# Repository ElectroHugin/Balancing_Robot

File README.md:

# Balancing_Robot

## Description
Self balancing robot with two wheels. Scope of functionality depends on sensors and is still work in progress.

## Materials
- ESP32 Dev Kit C V4 mit CP2102
- Later on custom board with ESP32-S3-WROOM
- SiliconLabs Uart-to-USB CP2102
- ~~Accelerometer / Gyroscope / Magnetometer BNO085~~
- Accelerometer / Gyroscope MPU6050
- VL53L0X Time-of-Flight (TOF) Laser distance sensor
- (HC-SR04 Ultrasound Module)
- (MAX7219 8x8 1 Dot Matrix MCU LED Display Module)
- ~~BMP180 Barometric Air Pressure and Temperature Sensor~~
- ~~DHT22 Temperature Sensor and Humidity Sensor~~
- ~~Photo LDR Resistor Diodes~~
- ~~L298N H-Bridge Motor Driver~~
- TB6612FNG Motor Driver
- USB-C PD with Battery
- ~~MT3608 DC-DC power supply adapter step up module~~
    ~~- Input voltage: 2V - 24V~~
    ~~- Output voltage: 3V - 28V~~
- ~~OR M2596S Step-down DC-DC Buck Converter~~
    ~~-  Input voltage: 4-40V~~
    ~~-  Output voltage: 3.3-24V~~
- JGA25-371 DC-Motor 12V with Hall-Encoder 65mm wheels

## Visuals
### 3D Model

### PCB Models

## Installation
WIP

## Usage
WIP

## License
Licenses under GNU GENERAL PUBLIC LICENSE Version 3, 29 June 2007

## Project status
Still at the beginning of project.

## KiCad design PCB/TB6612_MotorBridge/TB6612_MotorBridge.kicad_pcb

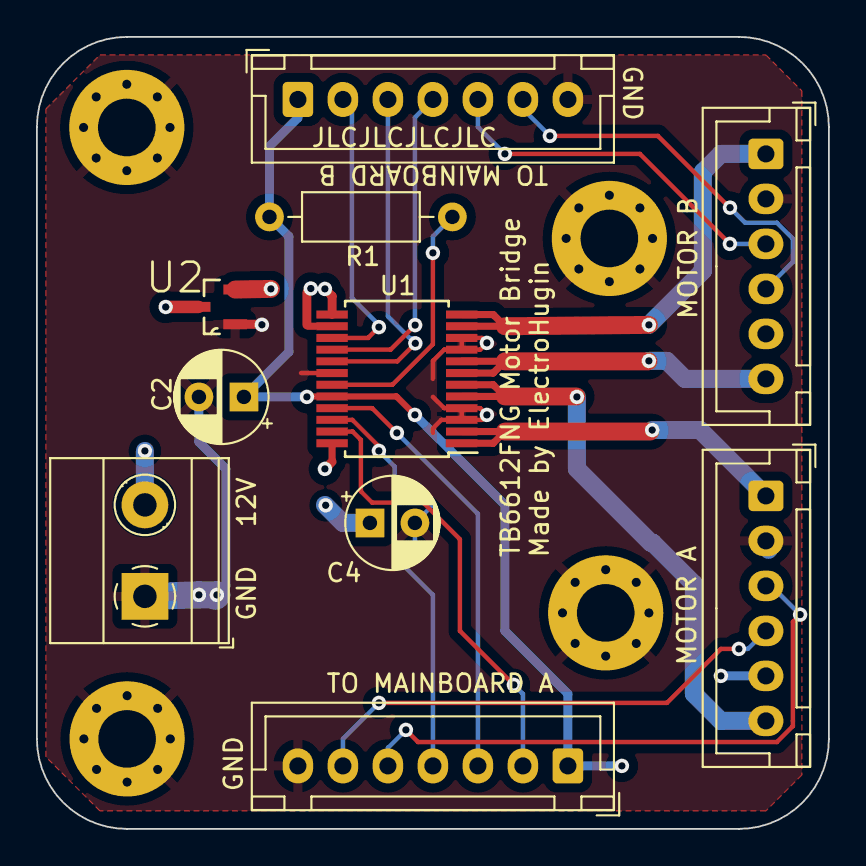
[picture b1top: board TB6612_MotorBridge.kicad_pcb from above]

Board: 4 copper layers, 44.0 x 44.0 mm, 14 parts (0 on the bottom side), 19 nets.

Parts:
C2, C4: 10u; CP_Radial_D5.0mm_P2.50mm
H1, H2, H3, H4: Hole_Pad; MountingHole_3.2mm_M3_Pad_Via
J1, J2: Conn_01x07; JST_XH_B7B-XH-A_1x07_P2.50mm_Vertical
J3: Screw_Terminal_01x02; TerminalBlock_Phoenix_MKDS-1,5-2-5.08_1x02_P5.08mm_Horizont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
J4, J5: Conn_01x06; JST_XH_B6B-XH-A_1x06_P2.50mm_Vertical
R1: 10K; R_Axial_DIN0207_L6.3mm_D2.5mm_P10.16mm_Horizontal
U1: TB6612FNG; SSOP-24_5.3x8.2mm_P0.65mm
U2: DMG3415U-7; SOT95P240X105-3N

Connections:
+3.3V: C2.1, J1.1, J2.1, J4.5, J5.5, R1.1, U1.20 (VCC)
+12V: C4.1, U1.13 (VM2), U1.14 (VM3), U1.24 (VM1), U2.2 (S)
/12VA: J3.2, U2.3 (D)
/A1: J1.3, U1.21 (AIN1)
/A2: J1.4, U1.22 (AIN2)
/B1: J2.3, U1.17 (BIN1)
/B2: J2.4, U1.16 (BIN2)
/EA1: J1.5, J4.3
/EA2: J1.6, J4.4
/EB1: J2.5, J5.3
/EB2: J2.6, J5.4
/MA1: J4.1, U1.1 (AO1), U1.2 (AO1)
/MA2: J4.6, U1.5 (AO2), U1.6 (AO2)
/MB1: J5.1, U1.11 (BO1), U1.12 (BO1)
/MB2: J5.6, U1.7 (BO2), U1.8 (BO2)
/PWM_A: J1.2, U1.23 (PWMA)
/PWM_B: J2.2, U1.15 (PWMB)
GND: C2.2, C4.2, H1.1, H2.1, H3.1, H4.1, J1.7, J2.7, J3.1, J4.2, J5.2, U1.3 (PGND1), U1.4 (PGND1), U1.9 (PGND2), U1.10 (PGND2), U1.18 (GND), U2.1 (G)
unnamed: R1.2, U1.19 (STBY)

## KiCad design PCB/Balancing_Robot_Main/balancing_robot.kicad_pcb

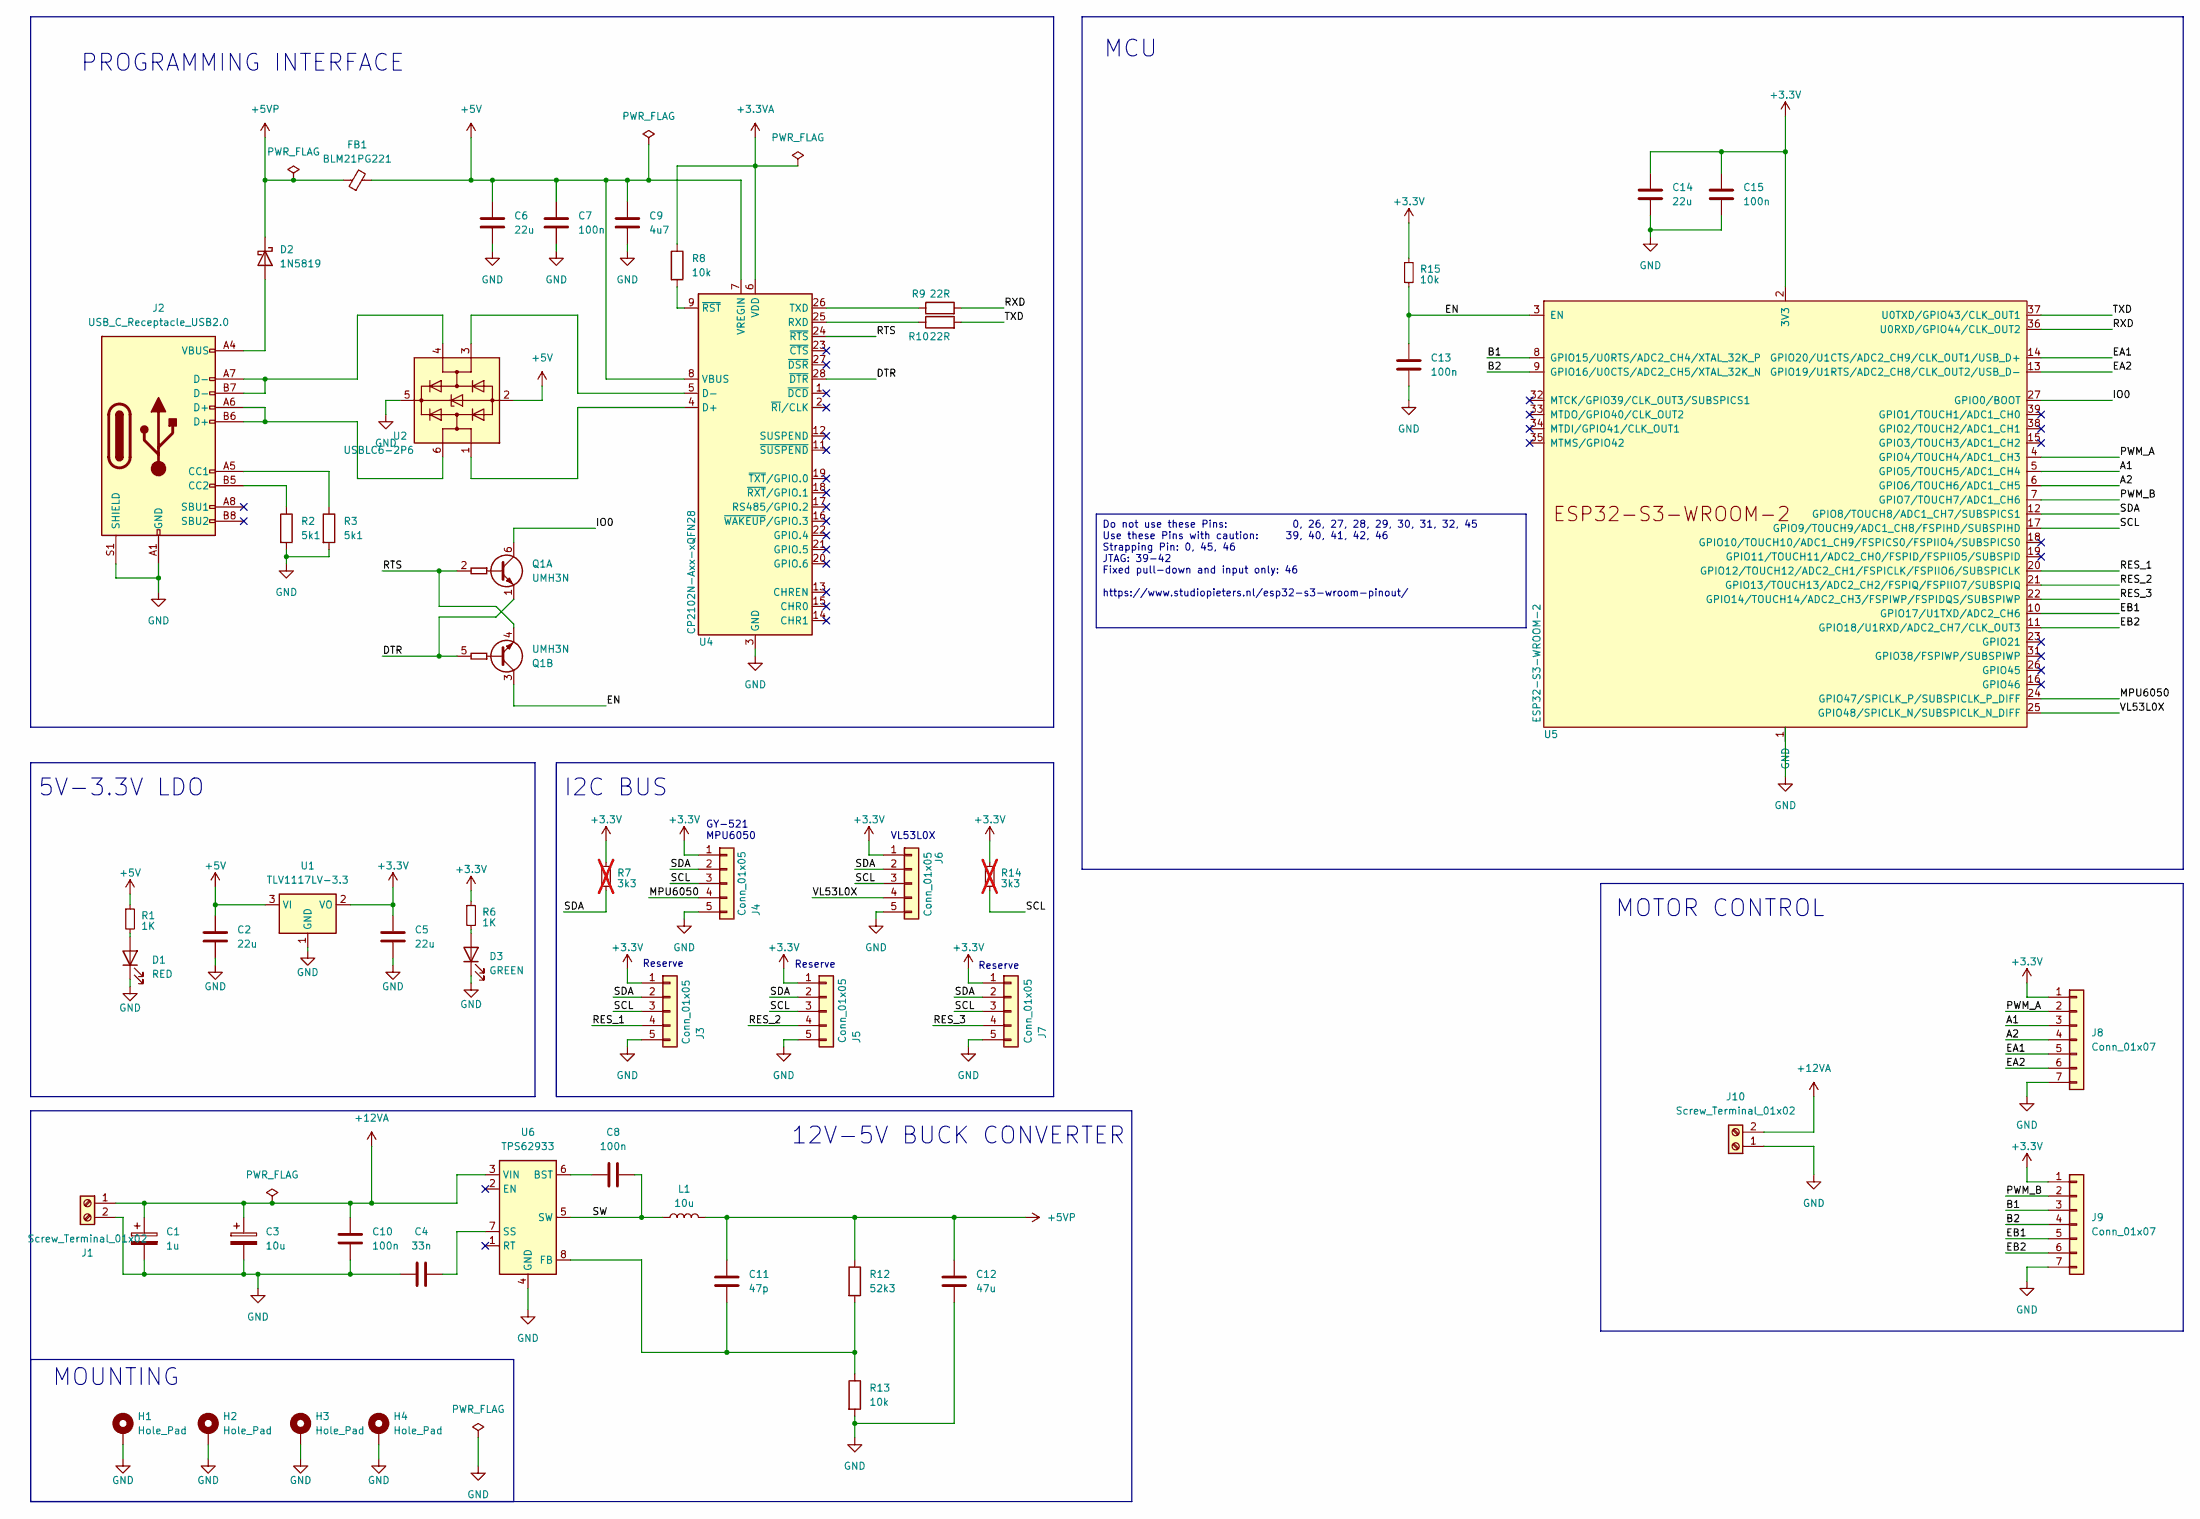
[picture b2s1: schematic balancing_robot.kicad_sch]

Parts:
C1: 1u; CP_Radial_D5.0mm_P2.50mm
C2, C5: 22u; C_1206_3216Metric
C3: 10u; CP_Radial_D5.0mm_P2.50mm
C4: 33n; C_1206_3216Metric
C6, C14: 22u; C_Disc_D5.0mm_W2.5mm_P5.00mm
C7, C13, C15: 100n; C_Disc_D5.0mm_W2.5mm_P5.00mm
C8, C10: 100n; C_1206_3216Metric
C9: 4u7; C_1206_3216Metric
C11: 47p; C_1206_3216Metric
C12: 47u; C_1206_3216Metric
D1: RED; LED_D3.0mm
D2: 1N5819; D_DO-41_SOD81_P10.16mm_Horizontal
D3: GREEN; LED_D3.0mm
FB1: BLM21PG221; L_0603_1608Metric
H1, H2, H3, H4: Hole_Pad; MountingHole_3.2mm_M3_Pad_Via
J1, J10: Screw_Terminal_01x02; TerminalBlock_Phoenix_MKDS-1,5-2-5.08_1x02_P5.08mm_Horizont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
J2: USB_C_Receptacle_USB2.0; USB_C_Receptacle_HRO_TYPE-C-31-M-12
J3, J4, J5, J6, J7: Conn_01x05; JST_XH_B5B-XH-AM_1x05_P2.50mm_Vertical
J8, J9: Conn_01x07; JST_XH_B7B-XH-A_1x07_P2.50mm_Vertical
L1: 10u; L_Bourns_SRR1208_12.7x12.7mm
Q1: UMH3N; SOT-363_SC-70-6
R1, R6: 1K; R_Axial_DIN0207_L6.3mm_D2.5mm_P10.16mm_Horizontal
R2, R3: 5k1; R_1206_3216Metric
R7, R14: 3k3; R_Axial_DIN0207_L6.3mm_D2.5mm_P10.16mm_Horizontal; not fitted
R8, R13, R15: 10k; R_1206_3216Metric
R9, R10: 22R; R_Axial_DIN0207_L6.3mm_D2.5mm_P10.16mm_Horizontal
R12: 52k3; R_1206_3216Metric
U1: TLV1117LV-3.3; SOT-223-3_TabPin2
U2: USBLC6-2P6; SOT-666
U4: CP2102N-Axx-xQFN28; QFN-28-1EP_5x5mm_P0.5mm_EP3.35x3.35mm
U5: ESP32-S3-WROOM-2
U6: TPS62933; SOT-583-8

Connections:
+3.3V: C5.1, C14.1, C15.1, J3.1, J4.1, J5.1, J6.1, J7.1, J8.1, J9.1, R6.1, R7.1, R14.1, R15.1, U1.2 (VO), U5.2 (3V3)
+3.3VA: R8.1, U4.6 (VDD)
+5V: C2.1, C6.1, C7.1, C9.1, FB1.2, R1.1, U1.3 (VI), U2.2 (GND), U4.7 (VREGIN), U4.8 (VBUS)
+5VP: C11.1, C12.1, D2.1 (K), FB1.1, L1.2, R12.1
+12VA: C1.1, C3.1, C10.2, J1.1, J10.2, U6.3 (VIN)
/A1: J8.3, U5.5 (GPIO5/TOUCH5/ADC1_CH4)
/A2: J8.4, U5.6 (GPIO6/TOUCH6/ADC1_CH5)
/B1: J9.3, U5.8 (GPIO15/U0RTS/ADC2_CH4/XTAL_32K_P)
/B2: J9.4, U5.9 (GPIO16/U0CTS/ADC2_CH5/XTAL_32K_N)
/DTR: Q1.1 (E1), Q1.5 (B2), U4.28 (~DTR)
/EA1: J8.5, U5.14 (GPIO20/U1CTS/ADC2_CH9/CLK_OUT1/USB_D+)
/EA2: J8.6, U5.13 (GPIO19/U1RTS/ADC2_CH8/CLK_OUT2/USB_D-)
/EB1: J9.5, U5.10 (GPIO17/U1TXD/ADC2_CH6)
/EB2: J9.6, U5.11 (GPIO18/U1RXD/ADC2_CH7/CLK_OUT3)
/EN: C13.1, Q1.3 (C2), R15.2, U5.3 (EN)
/IO0: Q1.6 (C1), U5.27 (GPIO0/BOOT)
/MPU6050: J4.4, U5.24 (GPIO47/SPICLK_P/SUBSPICLK_P_DIFF)
/PWM_A: J8.2, U5.4 (GPIO4/TOUCH4/ADC1_CH3)
/PWM_B: J9.2, U5.7 (GPIO7/TOUCH7/ADC1_CH6)
/RES_1: J3.4, U5.20 (GPIO12/TOUCH12/ADC2_CH1/FSPICLK/FSPIIO6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)
/RES_2: J5.4, U5.21 (GPIO13/TOUCH13/ADC2_CH2/FSPIQ/FSPIIO7/S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)
/RES_3: J7.4, U5.22 (GPIO14/TOUCH14/ADC2_CH3/FSPIWP/FSPIDQS/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)
/RTS: Q1.2 (B1), Q1.4 (E2), U4.24 (~RTS)
/RXD: R9.2, U5.36 (U0RXD/GPIO44/CLK_OUT2)
/SCL: J3.3, J4.3, J5.3, J6.3, J7.3, R14.2, U5.17 (GPIO9/TOUCH9/ADC1_CH8/FSPIHD/SUBSPIHD)
/SDA: J3.2, J4.2, J5.2, J6.2, J7.2, R7.2, U5.12 (GPIO8/TOUCH8/ADC1_CH7/SUBSPICS1)
/SW: C8.2, L1.1, U6.5 (SW)
/TXD: R10.2, U5.37 (U0TXD/GPIO43/CLK_OUT1)
/VL53L0X: J6.4, U5.25 (GPIO48/SPICLK_N/SUBSPICLK_N_DIFF)
GND: C1.2, C2.2, C3.2, C4.1, C5.2, C6.2, C7.2, C9.2, C10.1, C12.2, C13.2, C14.2, C15.2, D1.1 (K), D3.1 (K), H1.1, H2.1, H3.1, H4.1, J1.2, J2.A1 (GND), J2.A12 (GND), J2.B1 (GND), J2.B12 (GND), J2.S1 (SHIELD), J3.5, J4.5, J5.5, J6.5, J7.5, J8.7, J9.7, J10.1, R2.2, R3.2, R13.2, U1.1 (GND), U2.5 (VBUS), U4.3 (GND), U4.29 (GND), U5.1 (GND), U5.40 (GND), U5.41 (GND), U6.4 (GND)
unnamed: D1.2 (A), R1.2
unnamed: D2.2 (A), J2.A4 (VBUS), J2.A9 (VBUS), J2.B4 (VBUS), J2.B9 (VBUS)
unnamed: D3.2 (A), R6.2
unnamed: J2.A5 (CC1), R3.1
unnamed: J2.B5 (CC2), R2.1
unnamed: J2.A6 (D+), J2.B6 (D+), U2.6 (I/O1)
unnamed: J2.A7 (D-), J2.B7 (D-), U2.4 (I/O2)
unnamed: U2.1 (I/O1), U4.4 (D+)
unnamed: U2.3 (I/O2), U4.5 (D-)
unnamed: R10.1, U4.25 (RXD)
unnamed: R9.1, U4.26 (TXD)
unnamed: R8.2, U4.9 (~RST)
unnamed: C8.1, U6.6 (BST)
unnamed: C11.2, R12.2, R13.1, U6.8 (FB)
unnamed: C4.2, U6.7 (SS)

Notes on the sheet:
Do not use these Pins: 0, 26, 27, 28, 29, 30, 31, 32, 45 Use these Pins with caution: 39, 40, 41, 42, 46 Strapping Pin: 0, 45, 46 JTAG: 39-42 Fixed pull-down and input only: 46 https://www.studiopieters.nl/esp32-s3-wroom-pinout/
I2C BUS
GY-521 MPU6050
MCU
Reserve
VL53L0X
MOUNTING
12V-5V BUCK CONVERTER
5V-3.3V LDO
PROGRAMMING INTERFACE
MOTOR CONTROL

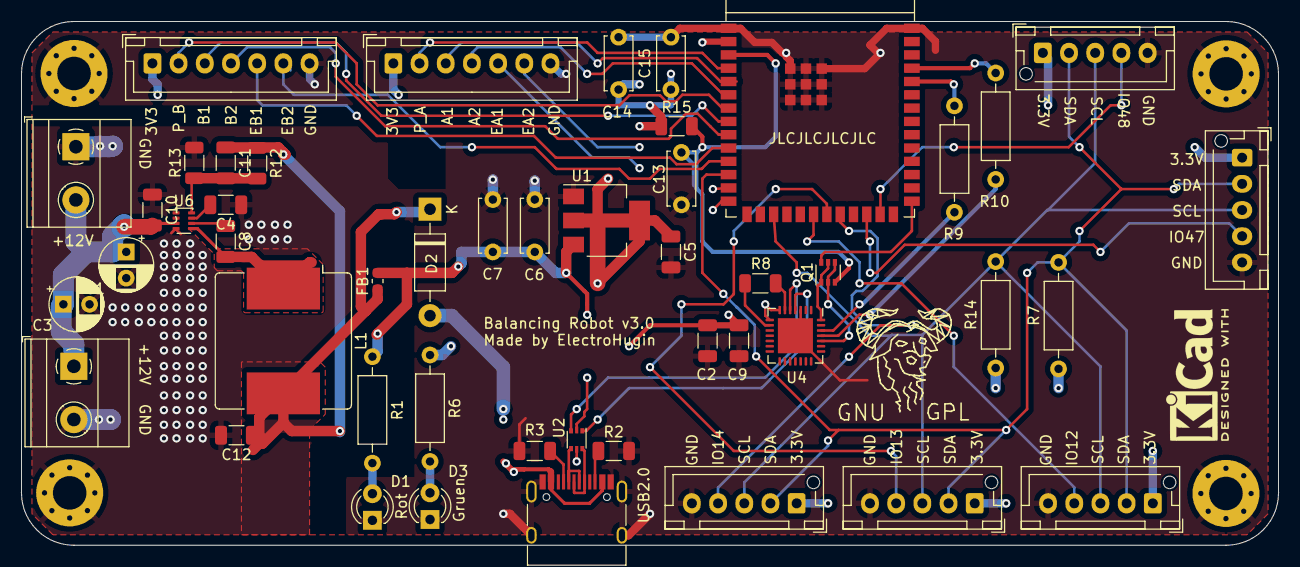
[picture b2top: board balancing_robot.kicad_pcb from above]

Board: 4 copper layers, 120.0 x 50.0 mm, 52 parts (0 on the bottom side), 45 nets.

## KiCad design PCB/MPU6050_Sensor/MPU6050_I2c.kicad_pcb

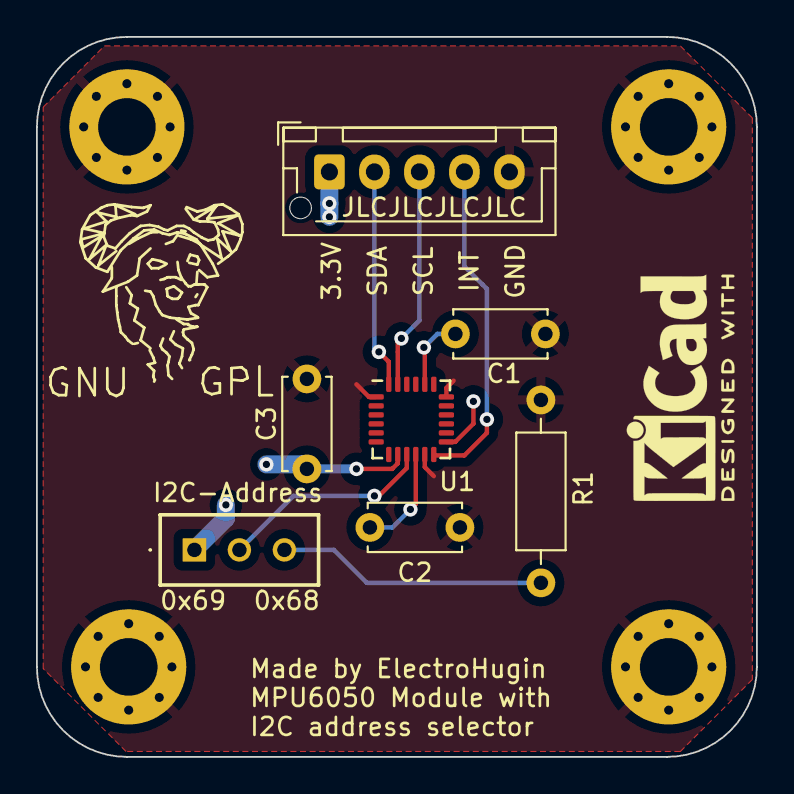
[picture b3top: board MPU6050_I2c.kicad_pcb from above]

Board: 4 copper layers, 40.0 x 40.0 mm, 11 parts (0 on the bottom side), 9 nets.

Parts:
C1: 2200p; C_Disc_D5.0mm_W2.5mm_P5.00mm
C2, C3: 0.1u; C_Disc_D5.0mm_W2.5mm_P5.00mm
H1, H2, H3, H4: Hole_Pad; MountingHole_3.2mm_M3_Pad_Via
J1: Conn_01x05; JST_XH_B5B-XH-AM_1x05_P2.50mm_Vertical
R1: 4k7; R_Axial_DIN0207_L6.3mm_D2.5mm_P10.16mm_Horizontal
SW1: SW_SPDT; SLW8839352AD
U1: MPU-6050; InvenSense_QFN-24_4x4mm_P0.5mm

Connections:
+3.3V: C3.2, J1.1, SW1.1 (A), U1.8 (VLOGIC), U1.13 (VDD)
/MPU6050: J1.4, U1.12 (INT)
/SCL: J1.3, U1.23 (SCL)
/SDA: J1.2, U1.24 (SDA)
GND: C1.2, C2.1, C3.1, H1.1, H2.1, H3.1, H4.1, J1.5, R1.2, U1.1 (CLKIN), U1.11 (FSYNC), U1.18 (GND)
unnamed: SW1.2 (B), U1.9 (AD0)
unnamed: R1.1, SW1.3 (C)
unnamed: C1.1, U1.20 (CPOUT)
unnamed: C2.2, U1.10 (REGOUT)

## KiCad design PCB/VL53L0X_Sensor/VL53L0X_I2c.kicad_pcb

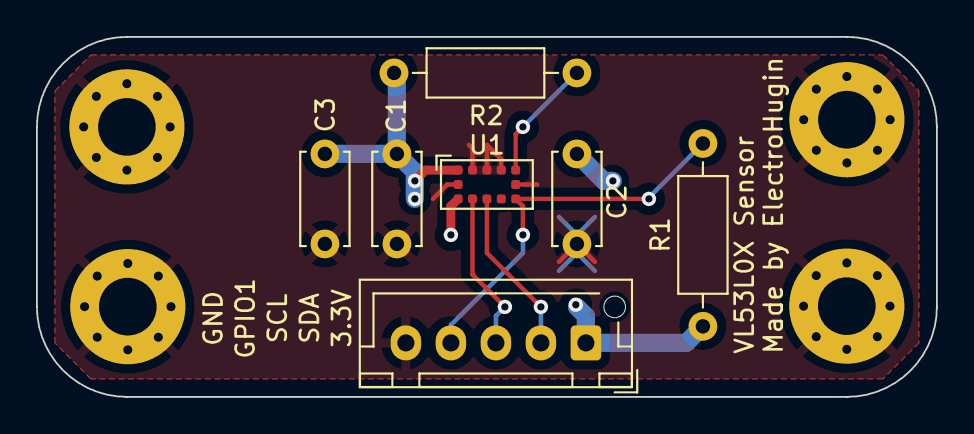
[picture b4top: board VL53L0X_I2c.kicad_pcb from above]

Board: 4 copper layers, 50.0 x 20.0 mm, 11 parts (0 on the bottom side), 6 nets.

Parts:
C1: 0.1u; C_Disc_D5.0mm_W2.5mm_P5.00mm
C2: 4.7u; C_Disc_D5.0mm_W2.5mm_P5.00mm
C3: 1u; C_Disc_D5.0mm_W2.5mm_P5.00mm
H1, H2, H3, H4: Hole_Pad; MountingHole_3.2mm_M3_Pad_Via
J1: Conn_01x05; JST_XH_B5B-XH-AM_1x05_P2.50mm_Vertical
R1, R2: 47k; R_Axial_DIN0207_L6.3mm_D2.5mm_P10.16mm_Horizontal
U1: VL53L1CXV0FY1; ST_VL53L1x

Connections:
+3.3V: C1.1, C2.1, C3.1, J1.1, R1.1, R2.1, U1.1 (AVDDVCSEL), U1.11 (AVDD)
/SCL: J1.3, U1.10 (SCL)
/SDA: J1.2, U1.9 (SDA)
/VL53L0X: J1.4, R1.2, U1.7 (GPIO1)
GND: C1.2, C2.2, C3.2, H1.1, H2.1, H3.1, H4.1, J1.5, U1.2 (AVSSVCSEL), U1.3 (GND), U1.4 (GND), U1.6 (GND), U1.12 (GND)
unnamed: R2.2, U1.5 (XSHUT)

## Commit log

2024-01-27 Configure SAST in `.gitlab-ci.yml`, creating this file if it does not already exist
2024-01-27 Add LICENSE
2024-01-27 Added Materials
2024-01-27 Added Sensors and Actuators
2024-01-28 Added Info about wheels and motor
2024-02-02 Added KiCad Schematic and some Datasheets
2024-02-02 Added BNO_0xx datasheet and schematic
2024-02-03 Added Datasheet motor and model drawing
2024-02-05 Initialized PlatformIO Project
2024-02-05 Added BNO Imu functionality
2024-02-08 Added Board Schematic and PCB and Code for MPU6050
2024-02-09 Added Sensor PCBs and experimented with MPU code
2024-02-10 Working Version of MPU6050 Library
2024-02-10 Working Version of ToFLib finished, cm and m still bugged
2024-02-10 Added Encoder counter for motor
2024-02-11 Restructured folders
2024-02-11 Added Options to platformio.ini
2024-02-11 Added Motor Bridge based on TB6612FNG
2024-02-12 Updated PCB Main and MotorBridge with Pins for Encoder
2024-02-12 Modified Readme
2024-02-12 Removed unneeded files
2024-02-12 Converted all vias to through-hole
2024-02-14 Added Visuals
2024-02-14 Changed number of pulses to count 4->2
2024-02-14 Added Connectivity to second Motor LH
